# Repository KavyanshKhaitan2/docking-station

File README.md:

# (Overengineered) Laptop Docking Station!

  [View in OnShape](https://cad.onshape.com/documents/6c290d74c1d15daba79eec04/w/3858ccf09c2f651529fab3b7/e/cec4245d48316d051146b3ca?renderMode=0&uiState=6a2cddf3cc68f1e0ff63f0b2)

A very cool laptop docking station with 9 USB-A 2.0 ports!

<div id="contents">

1. [Why?](#why)
2. [What can it do?](#what-can-it-do)
3. [Fallout Zine](#fallout-zine)
4. [PCB](#pcb)
   - [Mainboard](#mainboard)
   - [Left Daughterboard](#left-daugtherboard)
5. [Schematic](#schematic)
   - [Mainboard](#mainboard-1)
   - [Left Daughterboard](#left-daugtherboard-1)
   - [Right Daugtherboard](#right-daugtherboard)
   - [Front Daugtherboard](#front-daughterboard)
6. [3D](#3d)
   - [Main case](#main-case)
   - [Macropad assembly](#macropad-assembly)
   - [Macropad case](#macropad-case)
   - [ePaper assembly](#epaper-assembly)
   - [ePaper case](#epaper-case)
7. [Bill of Materials](#bom)

</div>

## Why?
My laptop only has 2 USB-A ports, which is honestly not enough especially when both of them are used up for a keyboard and mouse.

I made this docking station to change that.

Another reason I made this is that I kinda like taking my laptop with me and keep it on my lap while using it on the sofa sometimes, so a docking station kinda makes that easier so you only have to plug it in and then everything works!

<div align="center"><a href="#contents">Jump to contents</a></div>

## What can it do?
It has 9 USB ports, which you can connect whatever you want to. The USB ports are controlled using an Fe1.1s controller.

It also has an ESP32 and 2 controllable PWM case fans (with two mosfet so you can turn them completely off), to keep your laptop cool and prevent it from overheating.

I also added external power from a barrel jack, because the laptop wont be able to power so many USB ports, especially when things are connected to them.

There is also a programmable e-ink display, you can display the time, your notifications, the current speed of the fans, or even show specifically which USB ports are currently in use!

I also added a mini detachable macropad with three switches and a rotary encoder.

You can program the macropad's buttons to do whatever you want! The rotary encoder also works as a switch, so technically there are four switches. You can make the rotary encoder change the volume, fan speeds, etc!

The macropad is connected to the ESP32!

Oh and btw the ESP32 also supports WiFi incase you want it to show weather or something even when the laptop is turned off.

The ESP32 also knows exactly which ports are connected to devices at a time, so you can also make it show how many ports are in use, and how many are free, etc!

<div align="center"><a href="#contents">Jump to contents</a></div>

## Fallout Zine

[ [Download PDF](https://github.com/KavyanshKhaitan2/docking-station/raw/main/zine/Zine%20Print.pdf) ]

<div align="center"><a href="#contents">Jump to contents</a></div>

## PCB
<div align="center"><a href="https://kicanvas.org/?repo=https%3A%2F%2Fgithub.com%2FKavyanshKhaitan2%2Fdocking-station%2Ftree%2Fmain%2Fpcb%2F">View in KiCanvas</a></div>

### Mainboard

### Left Daugtherboard

The rest of the PCBs are very similar to the left daughterboard one, so I wont add them. If you still want to take a look at them, feel free to open the KiCanvas link!

<div align="center"><a href="#contents">Jump to contents</a></div>

## Schematic
<div align="center"><a href="https://kicanvas.org/?repo=https%3A%2F%2Fgithub.com%2FKavyanshKhaitan2%2Fdocking-station%2Ftree%2Fmain%2Fpcb%2F">View in KiCanvas</a></div>

### Mainboard

### Left daugtherboard

### Right daugtherboard

### Front daughterboard

<div align="center"><a href="#contents">Jump to contents</a></div>

## 3D
- [ [Download assembly as a STEP file](https://github.com/KavyanshKhaitan2/docking-station/blob/main/Final%20assembly.step) ]
- [ [Open Assembly in OnShape](https://cad.onshape.com/documents/6c290d74c1d15daba79eec04/w/3858ccf09c2f651529fab3b7/e/cec4245d48316d051146b3ca) ]

### Main case

- [View in OnShape](https://cad.onshape.com/documents/6c290d74c1d15daba79eec04/w/3858ccf09c2f651529fab3b7/e/84ca16973cb290fcea814d7e)
  - Part 1 (bottom) ([View STL in GitHub](https://github.com/KavyanshKhaitan2/docking-station/blob/main/production/3dp/Main%20Case/Main%20Case%20Thingy%20-%20Part%201.stl))
    - Print in black
    - Please print this part with supports!
  - Part 2 (top) ([View STL in GitHub](https://github.com/KavyanshKhaitan2/docking-station/blob/main/production/3dp/Main%20Case/Main%20Case%20Thingy%20-%20Part%202.stl))
    - Print in black

<div align="center"><a href="#contents">Jump to contents</a></div>

### Macropad assembly

- [View in OnShape](https://cad.onshape.com/documents/6c290d74c1d15daba79eec04/w/3858ccf09c2f651529fab3b7/e/eab1af3c6609ed024df62d84)

### Macropad case

- [View in OnShape](https://cad.onshape.com/documents/6c290d74c1d15daba79eec04/w/3858ccf09c2f651529fab3b7/e/cd5c69b8e6d2878261d109a7)
  - Part 1 (bottom) ([View STL in GitHub](https://github.com/KavyanshKhaitan2/docking-station/blob/main/production/3dp/Switches%20Case/Switches%20Case%20-%20Part%201.stl))
    - Print in black
  - Part 2 (top) ([View STL in GitHub](https://github.com/KavyanshKhaitan2/docking-station/blob/main/production/3dp/Switches%20Case/Switches%20Case%20-%20Part%202.stl))
    - Print in black
  - Screw ([View STL in GitHub](https://github.com/KavyanshKhaitan2/docking-station/blob/main/production/3dp/Switches%20Case/Switches%20Case%20-%20Screw%20(print%20x4).stl))
    - Print in black
    - Print x4
  - Accent (for top) ([View STL in GitHub](https://github.com/KavyanshKhaitan2/docking-station/blob/main/production/3dp/Switches%20Case/Switches%20Case%20-%20Accent.stl))
    - Print in filament closest to #8B2B2B.
      - 

<div align="center"><a href="#contents">Jump to contents</a></div>

### ePaper assembly

- [View in OnShape](https://cad.onshape.com/documents/6c290d74c1d15daba79eec04/w/3858ccf09c2f651529fab3b7/e/d050ad97f0686956ed070595)

### ePaper case

- Main part
  - [View in OnShape](https://cad.onshape.com/documents/6c290d74c1d15daba79eec04/w/3858ccf09c2f651529fab3b7/e/4e8279b7c40fa71bd8f46031)
  - Lid part (Lid) ([View STL in GitHub](https://github.com/KavyanshKhaitan2/docking-station/blob/main/production/3dp/ePaper%20Case/ePaper%20case%20-%20case-lid.stl))
  - Main part (Main) ([View STL in GitHub](https://github.com/KavyanshKhaitan2/docking-station/blob/main/production/3dp/ePaper%20Case/ePaper%20case%20-%20case-main.stl))
- Display angle-r
  - [View in OnShape](https://cad.onshape.com/documents/6c290d74c1d15daba79eec04/w/3858ccf09c2f651529fab3b7/e/b7b2b35c02b07108b093d455)
  - [View STL on GitHub](https://github.com/KavyanshKhaitan2/docking-station/blob/main/production/3dp/ePaper%20Case/Display%20angle-r%20-%20Part%201.stl)
    - Print in black
   
<div align="center"><a href="#contents">Jump to contents</a></div>

# BOM
The total BOM cost is ~167 USD.

- [ [View BOM.csv on GitHub](https://github.com/KavyanshKhaitan2/docking-station/blob/main/BOM.csv) ]
- [ [View BOM on Google Sheets (recommended)](https://docs.google.com/spreadsheets/d/10IkC0bF_AbRYA1OKs2MpRCw-cC0xSpxhRANUAgOrwtY/edit?gid=1294926540#gid=1294926540) ]

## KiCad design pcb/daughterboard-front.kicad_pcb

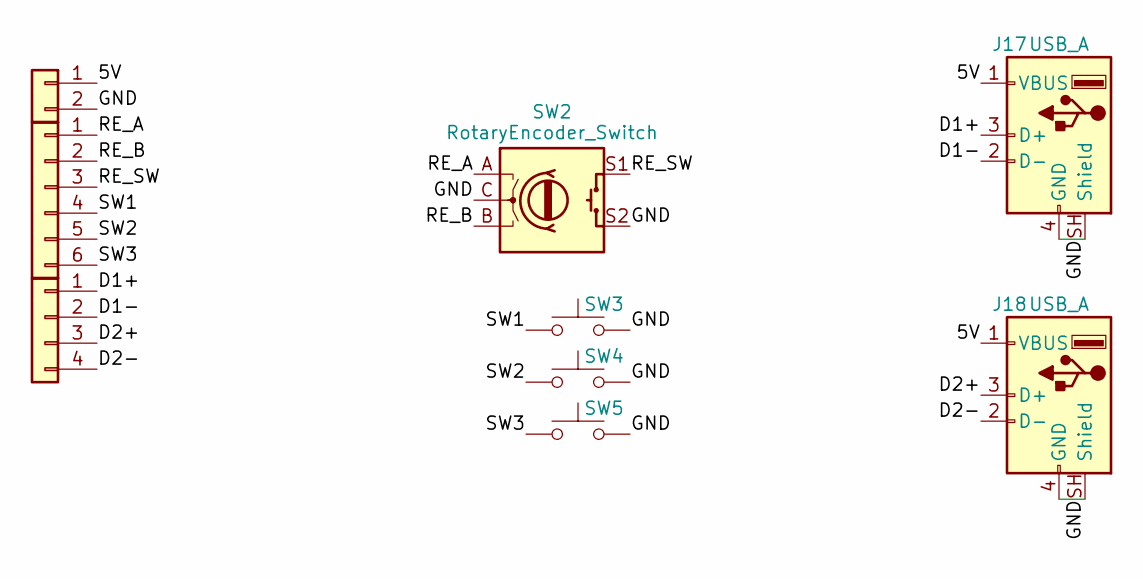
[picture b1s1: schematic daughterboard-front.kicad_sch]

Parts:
J16: Conn_01x06; PinHeader_1x06_P2.54mm_Vertical
J17, J18: USB_A; USB_A_Receptacle_GCT_USB1046
J26: Conn_01x04; Molex_200528-0040_1x04-1MP_P1.00mm_Horizontal
J31: Conn_01x02; SolderWire-4sqmm_1x02_P12mm_D3mm_OD6mm
SW2: RotaryEncoder_Switch; RotaryEncoder_Alps_EC11E-Switch_Vertical_H20mm
SW3, SW4, SW5: SW_Push; PinHeader_1x02_P2.54mm_Vertical

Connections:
/5V: J17.1 (VBUS), J18.1 (VBUS), J31.1
/D1+: J17.3 (D+), J26.1
/D1-: J17.2 (D-), J26.2
/D2+: J18.3 (D+), J26.3
/D2-: J18.2 (D-), J26.4
/GND: J17.4 (GND), J17.SH (Shield), J18.4 (GND), J18.SH (Shield), J31.2, SW2.C, SW2.S2, SW3.1, SW4.1, SW5.1
/RE_A: J16.1, SW2.A
/RE_B: J16.2, SW2.B
/RE_SW: J16.3, SW2.S1
/SW1: J16.4, SW3.2
/SW2: J16.5, SW4.2
/SW3: J16.6, SW5.2

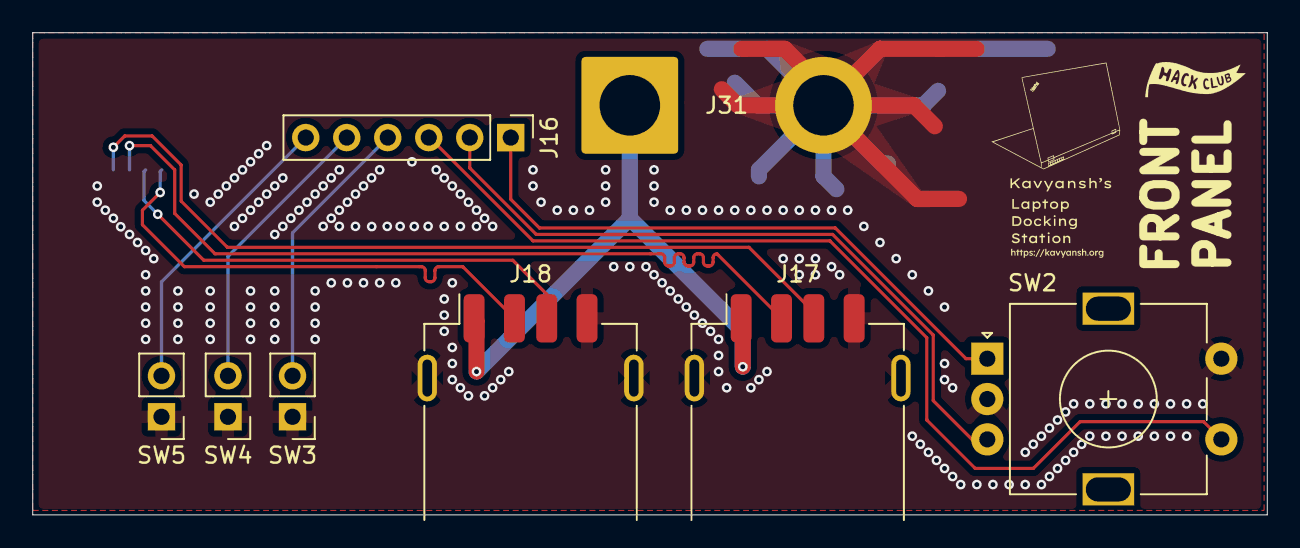
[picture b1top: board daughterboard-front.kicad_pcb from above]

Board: 2 copper layers, 76.5 x 29.9 mm, 9 parts (1 on the bottom side), 12 nets.

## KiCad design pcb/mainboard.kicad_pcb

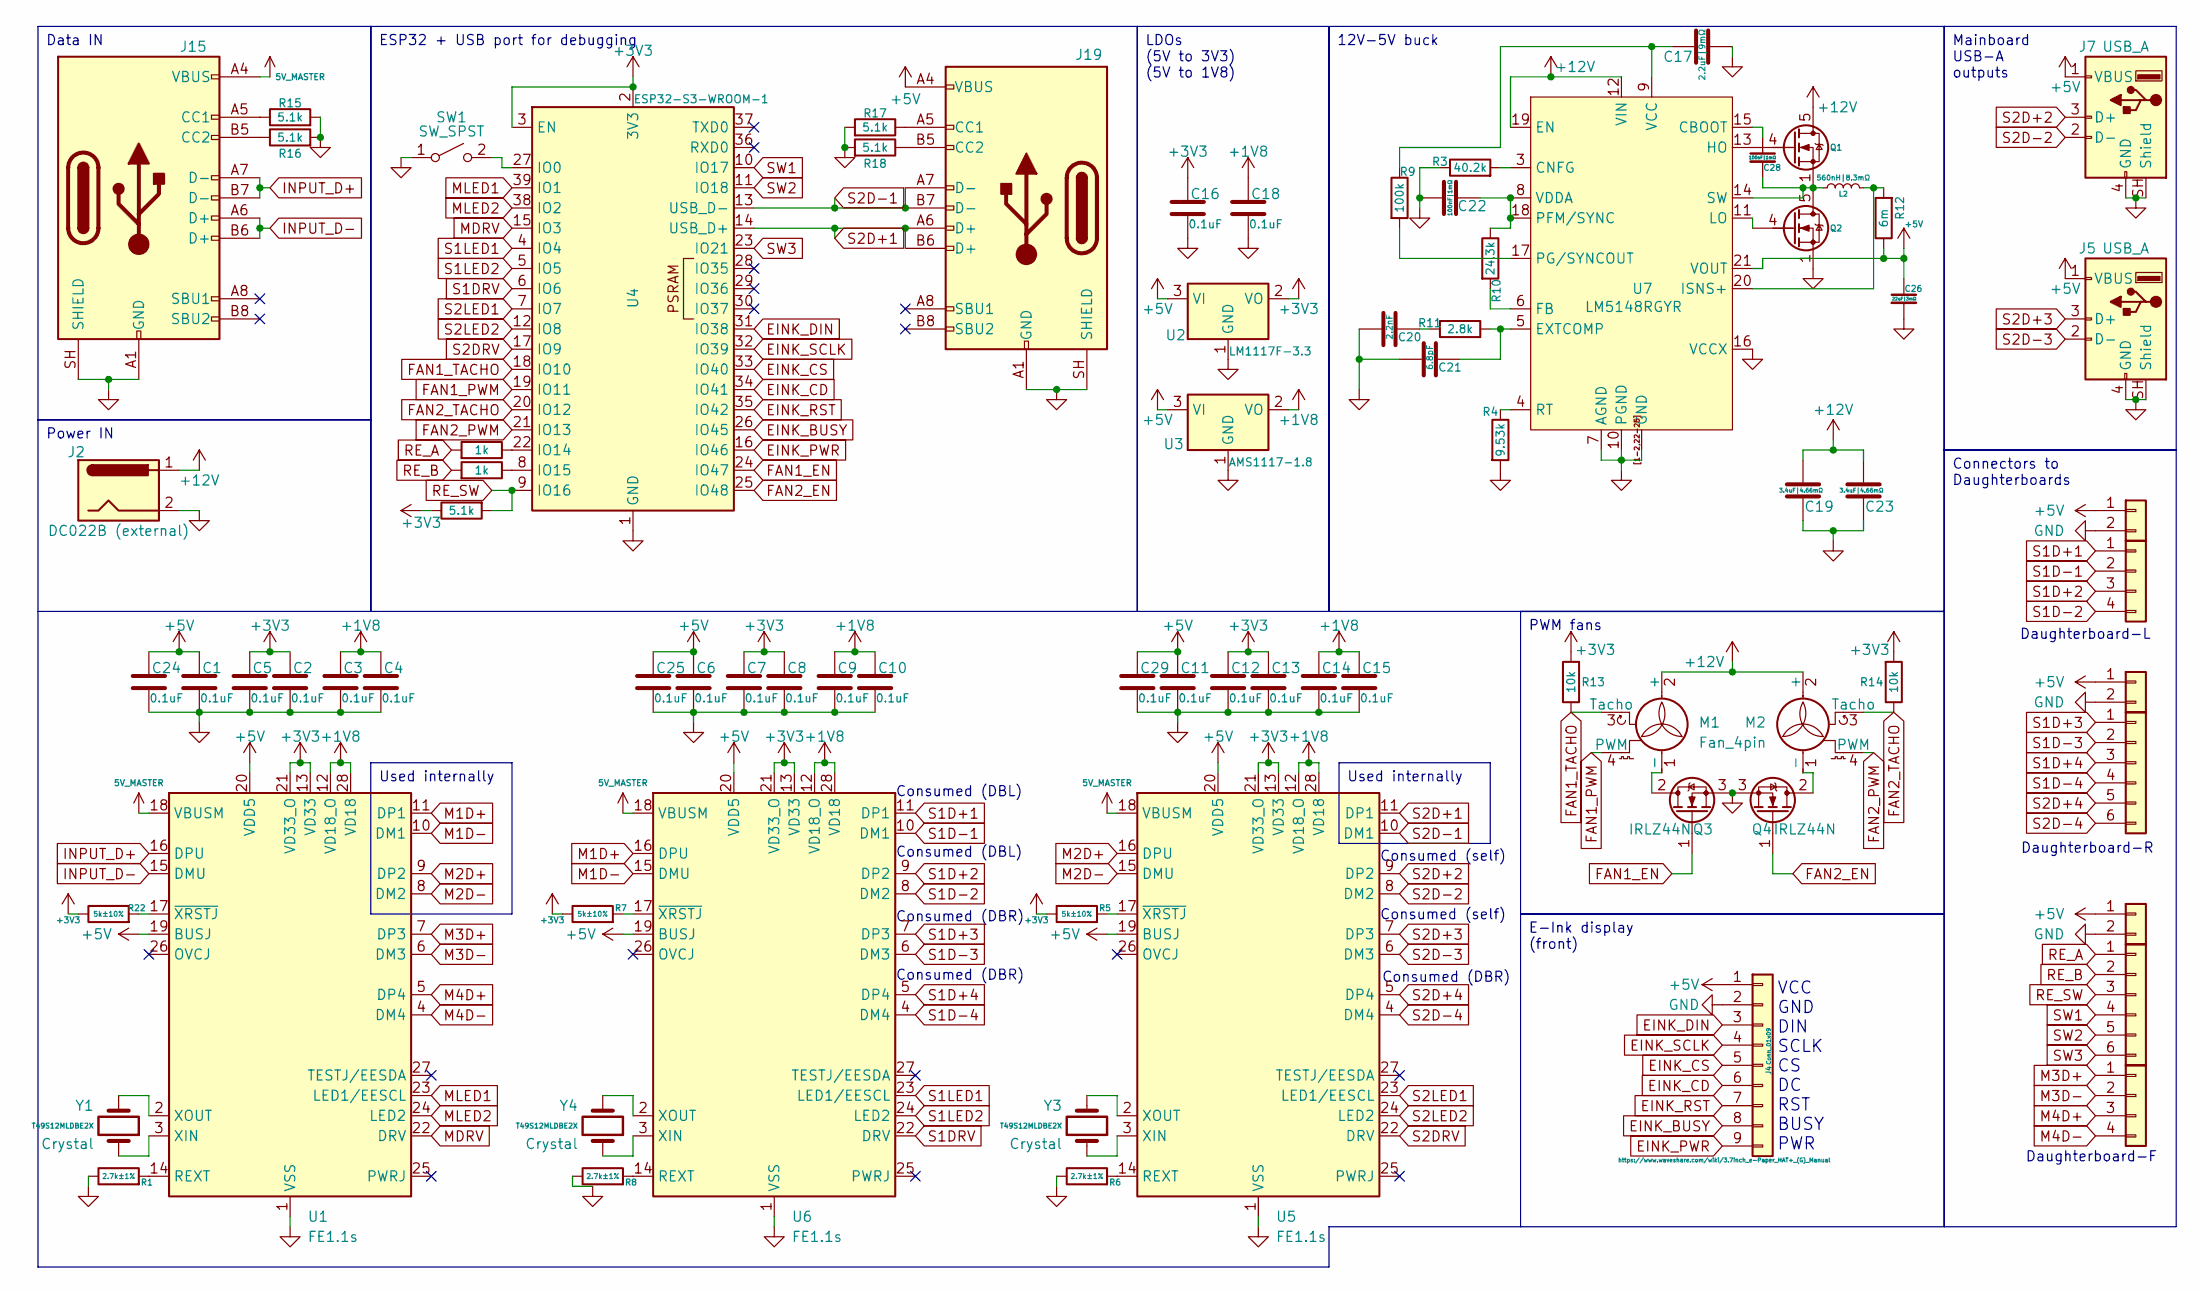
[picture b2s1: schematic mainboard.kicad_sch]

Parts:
C1, C2, C3, C4, C5, C6, C7, C8, C9, C10, C11, C12, C13, C14, C15, C16, C18, C24, C25, C29: 0.1uF; C_1206_3216Metric_Pad1.33x1.80mm_HandSolder
C17: 2.2uF|9mΩ; C_0603_1608Metric_Pad1.08x0.95mm_HandSolder
C19, C23: 3.4uF|4.66mΩ; C_1206_3216Metric_Pad1.33x1.80mm_HandSolder
C20: 2.2nF; C_0805_2012Metric_Pad1.18x1.45mm_HandSolder
C21: 6.8pF; C_0603_1608Metric_Pad1.08x0.95mm_HandSolder
C22, C28: 100nF|1mΩ; C_0402_1005Metric_Pad0.74x0.62mm_HandSolder
C26: 22uF|3mΩ; C_0805_2012Metric_Pad1.18x1.45mm_HandSolder
J2: DC022B (external); SolderWire-4sqmm_1x02_P12mm_D3mm_OD6mm
J4: Conn_01x09; JST_PH_B9B-PH-K_1x09_P2.00mm_Vertical
J5, J7: USB_A; USB_A_Receptacle_GCT_USB1046
J10: Conn_01x06; JUSHUO_AFA07-S06FCA-00_1x6-1MP_P1.0mm_Horizontal
J11: Conn_01x06; PinHeader_1x06_P2.54mm_Vertical
J15, J19: USB_C_Receptacle_USB2.0_16P; USB_C_Receptacle_HRO_TYPE-C-31-M-12
J20, J24, J27: Conn_01x02; SolderWire-4sqmm_1x02_P12mm_D3mm_OD6mm
J21, J25: Conn_01x04; Molex_200528-0040_1x04-1MP_P1.00mm_Horizontal
L2: 560nH|8.3mΩ; L_Coilcraft_XAL5020-XXX
M1, M2: Fan_4pin; FanPinHeader_1x04_P2.54mm_Vertical
Q1, Q2: CSD17579Q5A; TDSON-8-1
Q3, Q4: IRLZ44N; TO-220-3_Vertical
R1, R6, R8: 2.7k±1%; R_1206_3216Metric_Pad1.30x1.75mm_HandSolder
R3: 40.2k; R_1206_3216Metric_Pad1.30x1.75mm_HandSolder
R4: 9.53k; R_1206_3216Metric_Pad1.30x1.75mm_HandSolder
R5, R7, R22: 5k±10%; R_1206_3216Metric_Pad1.30x1.75mm_HandSolder
R9: 100k; R_1206_3216Metric_Pad1.30x1.75mm_HandSolder
R10: 24.3k; R_1206_3216Metric_Pad1.30x1.75mm_HandSolder
R11: 2.8k; R_1206_3216Metric_Pad1.30x1.75mm_HandSolder
R12: 6m; R_1206_3216Metric_Pad1.30x1.75mm_HandSolder
R13, R14: 10k; R_1206_3216Metric_Pad1.30x1.75mm_HandSolder
R15, R16, R17, R18, R21: 5.1k; R_1206_3216Metric_Pad1.30x1.75mm_HandSolder
R19, R20: 1k; R_1206_3216Metric_Pad1.30x1.75mm_HandSolder
SW1: SW_SPST; SW_SPST_Omron_B3F-50xx
U1, U5, U6: FE1.1s; SSOP-28_3.9x9.9mm_P0.635mm
U2: LM1117F-3.3; SOT-89-3_Handsoldering
U3: AMS1117-1.8; SOT-89-3_Handsoldering
U4: ESP32-S3-WROOM-1
U7: LM5148RGYR; Texas_RGY_R-PVQFN-N24_EP2.05x3.1mm_ThermalVias
Y1, Y3, Y4: T49S12MLDBE2X; Crystal_HC49-4H_Vertical

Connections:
5V_MASTER: J15.A4 (VBUS), J15.A9 (VBUS), J15.B4 (VBUS), J15.B9 (VBUS), U1.18 (VBUSM), U5.18 (VBUSM), U6.18 (VBUSM)
+1V8: C3.1, C4.1, C9.1, C10.1, C14.1, C15.1, C18.1, U1.12 (VD18_O), U1.28 (VD18), U3.2 (VO), U5.12 (VD18_O), U5.28 (VD18), U6.12 (VD18_O), U6.28 (VD18)
+3V3: C2.1, C5.1, C7.1, C8.1, C12.1, C13.1, C16.1, R5.1, R7.1, R13.2, R14.2, R21.1, R22.1, U1.13 (VD33), U1.21 (VD33_O), U2.2 (VO), U4.2 (3V3), U4.3 (EN), U5.13 (VD33), U5.21 (VD33_O), U6.13 (VD33), U6.21 (VD33_O)
+5V: C1.1, C6.1, C11.1, C24.1, C25.1, C26.1, C29.1, J4.1, J5.1 (VBUS), J7.1 (VBUS), J19.A4 (VBUS), J19.A9 (VBUS), J19.B4 (VBUS), J19.B9 (VBUS), J20.1, J24.1, J27.1, R12.1, U1.19 (BUSJ), U1.20 (VDD5), U2.3 (VI), U3.3 (VI), U5.19 (BUSJ), U5.20 (VDD5), U6.19 (BUSJ), U6.20 (VDD5), U7.21 (VOUT)
+12V: C19.2, C23.2, J2.1, M1.2 (+), M2.2 (+), Q1.5 (D), U7.12 (VIN), U7.19 (EN)
EINK_BUSY: J4.8, U4.26 (IO45)
EINK_CD: J4.6, U4.34 (IO41)
EINK_CS: J4.5, U4.33 (IO40)
EINK_DIN: J4.3, U4.31 (IO38)
EINK_PWR: J4.9, U4.16 (IO46)
EINK_RST: J4.7, U4.35 (IO42)
EINK_SCLK: J4.4, U4.32 (IO39)
FAN1_EN: Q3.1 (G), U4.24 (IO47)
FAN1_PWM: M1.4 (PWM), U4.19 (IO11)
FAN1_TACHO: M1.3 (Tacho), R13.1, U4.18 (IO10)
FAN2_EN: Q4.1 (G), U4.25 (IO48)
FAN2_PWM: M2.4 (PWM), U4.21 (IO13)
FAN2_TACHO: M2.3 (Tacho), R14.1, U4.20 (IO12)
GND: C1.2, C2.2, C3.2, C4.2, C5.2, C6.2, C7.2, C8.2, C9.2, C10.2, C11.2, C12.2, C13.2, C14.2, C15.2, C16.2, C17.1, C18.2, C19.1, C20.2, C21.2, C22.2, C23.1, C24.2, C25.2, C26.2, C29.2, J2.2, J4.2, J5.4 (GND), J5.SH (Shield), J7.4 (GND), J7.SH (Shield), J15.A1 (GND), J15.A12 (GND), J15.B1 (GND), J15.B12 (GND), J15.SH (SHIELD), J19.A1 (GND), J19.A12 (GND), J19.B1 (GND), J19.B12 (GND), J19.SH (SHIELD), J20.2, J24.2, J27.2, Q2.1 (S), Q2.2 (S), Q2.3 (S), Q3.3 (S), Q4.3 (S), R1.1, R3.1, R4.2, R6.1, R8.1, R15.2, R16.2, R17.2, R18.2, SW1.1 (A), U1.1 (VSS), U2.1 (GND), U3.1 (GND), U4.1 (GND), U4.40 (GND), U4.41 (GND), U5.1 (VSS), U6.1 (VSS), U7.1 (GND), U7.2 (GND), U7.7 (AGND), U7.10 (PGND), U7.16 (VCCX), U7.22 (GND), U7.23 (GND), U7.24 (GND), U7.25 (GND), U7.[1-2,22-25] (GND)
INPUT_D+: J15.A7 (D-), J15.B7 (D-), U1.16 (DPU)
INPUT_D-: J15.A6 (D+), J15.B6 (D+), U1.15 (DMU)
M1D+: U1.11 (DP1), U6.16 (DPU)
M1D-: U1.10 (DM1), U6.15 (DMU)
M2D+: U1.9 (DP2), U5.16 (DPU)
M2D-: U1.8 (DM2), U5.15 (DMU)
M3D+: J25.1, U1.7 (DP3)
M3D-: J25.2, U1.6 (DM3)
M4D+: J25.3, U1.5 (DP4)
M4D-: J25.4, U1.4 (DM4)
MDRV: U1.22 (DRV), U4.15 (IO3)
MLED1: U1.23 (LED1/EESCL), U4.39 (IO1)
MLED2: U1.24 (LED2), U4.38 (IO2)
unnamed: C20.1, R11.1
unnamed: J15.A5 (CC1), R15.1
unnamed: J15.B5 (CC2), R16.1
unnamed: J19.A5 (CC1), R17.1
unnamed: J19.B5 (CC2), R18.1
unnamed: M1.1 (-), Q3.2 (D)
unnamed: M2.1 (-), Q4.2 (D)
unnamed: Q1.4 (G), U7.13 (HO)
unnamed: C28.2, L2.1, Q1.1 (S), Q1.2 (S), Q1.3 (S), Q2.5 (D), U7.14 (SW)
unnamed: Q2.4 (G), U7.11 (LO)
unnamed: SW1.2 (B), U4.27 (IO0)
unnamed: R1.2, U1.14 (REXT)
unnamed: U1.3 (XIN), Y1.1
unnamed: U1.2 (XOUT), Y1.2
unnamed: R22.2, U1.17 (~XRSTJ)
unnamed: R19.1, U4.22 (IO14)
unnamed: R20.1, U4.8 (IO15)
unnamed: R6.2, U5.14 (REXT)
unnamed: U5.3 (XIN), Y3.1
unnamed: U5.2 (XOUT), Y3.2
unnamed: R5.2, U5.17 (~XRSTJ)
unnamed: R8.2, U6.14 (REXT)
unnamed: U6.3 (XIN), Y4.1
unnamed: U6.2 (XOUT), Y4.2
unnamed: R7.2, U6.17 (~XRSTJ)
unnamed: C28.1, U7.15 (CBOOT)
unnamed: R3.2, U7.3 (CNFG)
unnamed: C21.1, R11.2, U7.5 (EXTCOMP)
unnamed: R10.2, U7.6 (FB)
unnamed: L2.2, R12.2, U7.20 (ISNS+)
unnamed: C22.1, R10.1, U7.8 (VDDA), U7.18 (PFM/SYNC)
unnamed: R9.2, U7.17 (PG/SYNCOUT)
unnamed: R4.1, U7.4 (RT)
unnamed: C17.2, R9.1, U7.9 (VCC)
RE_A: J11.1, R19.2
RE_B: J11.2, R20.2
RE_SW: J11.3, R21.2, U4.9 (IO16)
S1D+1: J21.1, U6.11 (DP1)
S1D+2: J21.3, U6.9 (DP2)
S1D+3: J10.1, U6.7 (DP3)
S1D+4: J10.3, U6.5 (DP4)
S1D-1: J21.2, U6.10 (DM1)
S1D-2: J21.4, U6.8 (DM2)
S1D-3: J10.2, U6.6 (DM3)
S1D-4: J10.4, U6.4 (DM4)
S1DRV: U4.6 (IO6), U6.22 (DRV)
S1LED1: U4.4 (IO4), U6.23 (LED1/EESCL)
S1LED2: U4.5 (IO5), U6.24 (LED2)
S2D+1: J19.A6 (D+), J19.B6 (D+), U4.14 (USB_D+), U5.11 (DP1)
S2D+2: J7.3 (D+), U5.9 (DP2)
S2D+3: J5.3 (D+), U5.7 (DP3)
S2D+4: J10.5, U5.5 (DP4)
S2D-1: J19.A7 (D-), J19.B7 (D-), U4.13 (USB_D-), U5.10 (DM1)
S2D-2: J7.2 (D-), U5.8 (DM2)
S2D-3: J5.2 (D-), U5.6 (DM3)
S2D-4: J10.6, U5.4 (DM4)
S2DRV: U4.17 (IO9), U5.22 (DRV)
S2LED1: U4.7 (IO7), U5.23 (LED1/EESCL)
S2LED2: U4.12 (IO8), U5.24 (LED2)
SW1: J11.4, U4.10 (IO17)
SW2: J11.5, U4.11 (IO18)
SW3: J11.6, U4.23 (IO21)

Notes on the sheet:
Consumed (DBR)
Consumed (self)
Daughterboard-F
Consumed (DBL)
Daughterboard-R
VCC GND DIN SCLK CS DC RST BUSY PWR
Daughterboard-L
Used internally
Mainboard USB-A outputs
E-Ink display (front)
Data IN
Connectors to Daughterboards
ESP32 + USB port for debugging
Power IN
PWM fans
LDOs (5V to 3V3) (5V to 1V8)
12V-5V buck

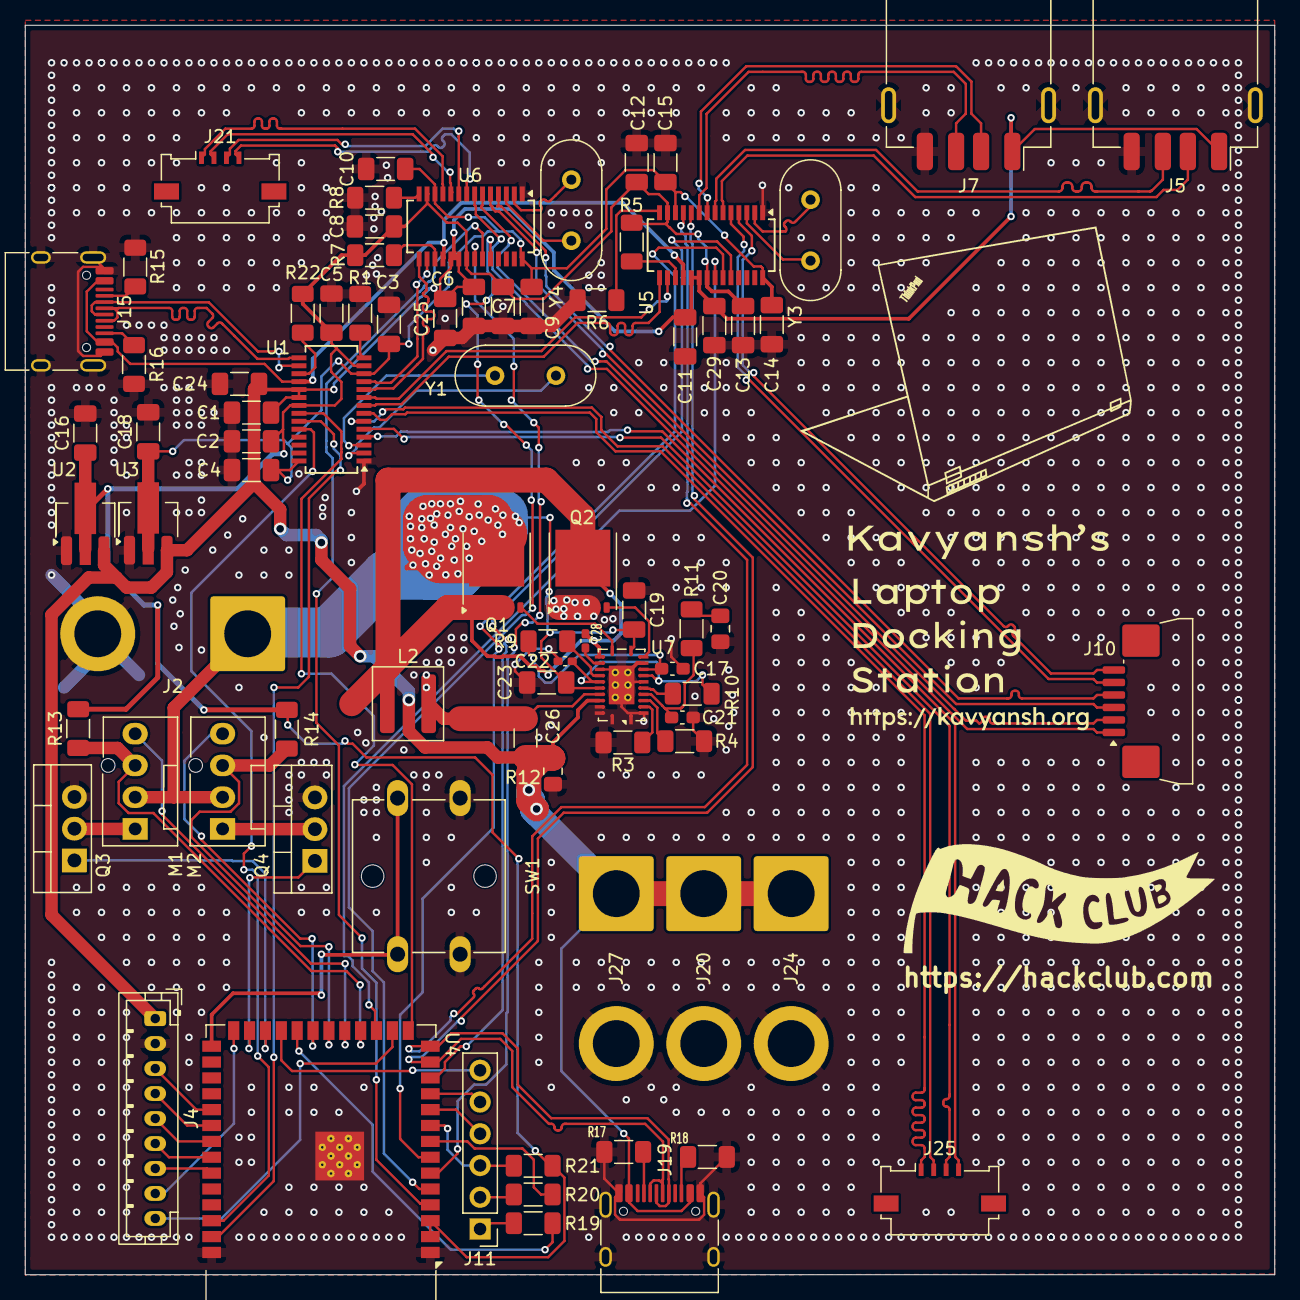
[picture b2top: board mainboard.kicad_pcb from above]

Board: 2 copper layers, 100.0 x 100.0 mm, 80 parts (0 on the bottom side), 94 nets.

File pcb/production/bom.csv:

Designator,Footprint,Quantity,Value,LCSC Part #
"C1, C10, C11, C12, C13, C14, C15, C16, C18, C2, C24, C25, C29, C3, C4, C5, C6, C7, C8, C9",1206,20,0.1uF,
C17,0603,1,2.2uF|9mΩ,
"C19, C23",1206,2,3.4uF|4.66mΩ,
C20,0805,1,2.2nF,
C21,0603,1,6.8pF,
"C22, C28",0402,2,100nF|1mΩ,
C26,0805,1,22uF|3mΩ,
J10,JUSHUO_AFA07-S06FCA-00_1x6-1MP_P1.0mm_Horizontal,1,Conn_01x06,
J11,PinHeader_1x06_P2.54mm_Vertical,1,Conn_01x06,
"J15, J19",USB_C_Receptacle_HRO_TYPE-C-31-M-12,2,USB_C_Receptacle_USB2.0_16P,
J2,SolderWire-4sqmm_1x02_P12mm_D3mm_OD6mm,1,DC022B (external),
"J20, J24, J27",SolderWire-4sqmm_1x02_P12mm_D3mm_OD6mm,3,Conn_01x02,
"J21, J25",Molex_200528-0040_1x04-1MP_P1.00mm_Horizontal,2,Conn_01x04,
J4,JST_PH_B9B-PH-K_1x09_P2.00mm_Vertical,1,Conn_01x09,
"J5, J7",USB_A_Receptacle_GCT_USB1046,2,USB_A,
L2,L_Coilcraft_XAL5020-XXX,1,560nH|8.3mΩ,
"M1, M2",FanPinHeader_1x04_P2.54mm_Vertical,2,Fan_4pin,
"Q1, Q2",TDSON-8-1,2,CSD17579Q5A,
"Q3, Q4",TO-220-3_Vertical,2,IRLZ44N,
"R1, R6, R8",1206,3,2.7k±1%,
R10,1206,1,24.3k,
R11,1206,1,2.8k,
R12,1206,1,6m,
"R13, R14",1206,2,10k,
"R15, R16, R17, R18, R21",1206,5,5.1k,
"R19, R20",1206,2,1k,
"R22, R5, R7",1206,3,5k±10%,
R3,1206,1,40.2k,
R4,1206,1,9.53k,
R9,1206,1,100k,
SW1,SW_SPST_Omron_B3F-50xx,1,SW_SPST,
"U1, U5, U6",SSOP-28_3.9x9.9mm_P0.635mm,3,FE1.1s,
U2,SOT-89-3_Handsoldering,1,LM1117F-3.3,
U3,SOT-89-3_Handsoldering,1,AMS1117-1.8,
U4,ESP32-S3-WROOM-1,1,ESP32-S3-WROOM-1,
U7,Texas_RGY_R-PVQFN-N24_EP2.05x3.1mm_ThermalVias,1,LM5148RGYR,
"Y1, Y3, Y4",Crystal_HC49-4H_Vertical,3,T49S12MLDBE2X,

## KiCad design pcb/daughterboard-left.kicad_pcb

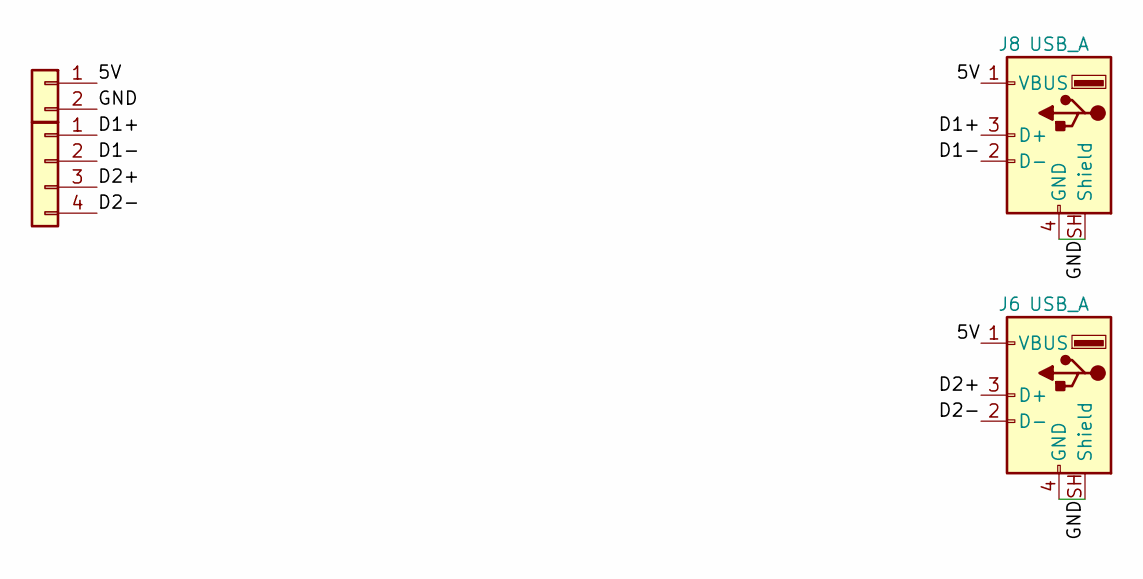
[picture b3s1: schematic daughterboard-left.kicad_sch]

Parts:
J6, J8: USB_A; USB_A_Receptacle_GCT_USB1046
J22: Conn_01x02; SolderWire-4sqmm_1x02_P12mm_D3mm_OD6mm
J23: Conn_01x04; Molex_200528-0040_1x04-1MP_P1.00mm_Horizontal

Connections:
/5V: J6.1 (VBUS), J8.1 (VBUS), J22.1
/D1+: J8.3 (D+), J23.1
/D1-: J8.2 (D-), J23.2
/D2+: J6.3 (D+), J23.3
/D2-: J6.2 (D-), J23.4
/GND: J6.4 (GND), J6.SH (Shield), J8.4 (GND), J8.SH (Shield), J22.2

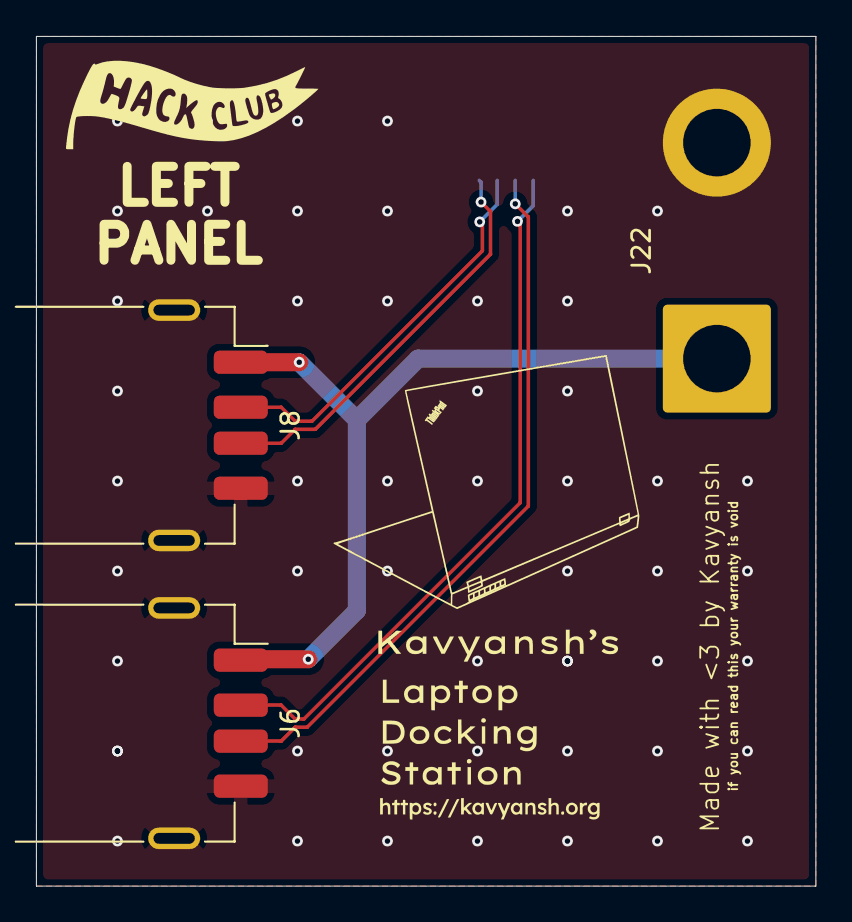
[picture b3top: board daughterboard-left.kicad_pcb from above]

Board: 2 copper layers, 43.3 x 47.2 mm, 4 parts (1 on the bottom side), 6 nets.

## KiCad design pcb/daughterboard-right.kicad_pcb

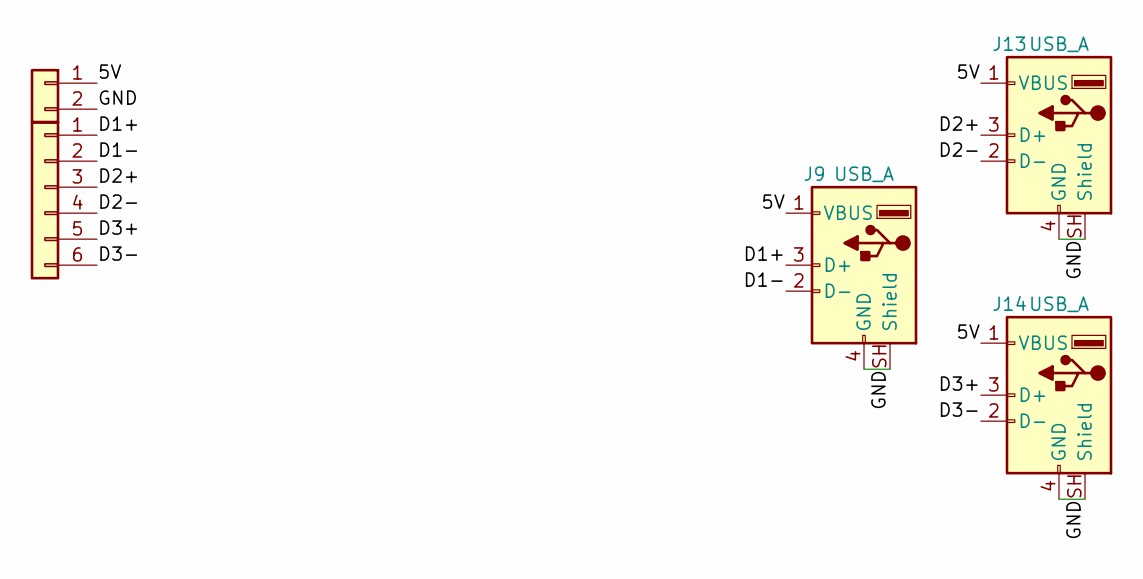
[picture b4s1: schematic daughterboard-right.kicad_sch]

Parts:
J9, J13, J14: USB_A; USB_A_Receptacle_GCT_USB1046
J12: Conn_01x06; JUSHUO_AFA07-S06FCA-00_1x6-1MP_P1.0mm_Horizontal
J30: Conn_01x02; SolderWire-4sqmm_1x02_P12mm_D3mm_OD6mm

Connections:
/5V: J9.1 (VBUS), J13.1 (VBUS), J14.1 (VBUS), J30.1
/D1+: J9.3 (D+), J12.1
/D1-: J9.2 (D-), J12.2
/D2+: J12.3, J13.3 (D+)
/D2-: J12.4, J13.2 (D-)
/D3+: J12.5, J14.3 (D+)
/D3-: J12.6, J14.2 (D-)
/GND: J9.4 (GND), J9.SH (Shield), J13.4 (GND), J13.SH (Shield), J14.4 (GND), J14.SH (Shield), J30.2

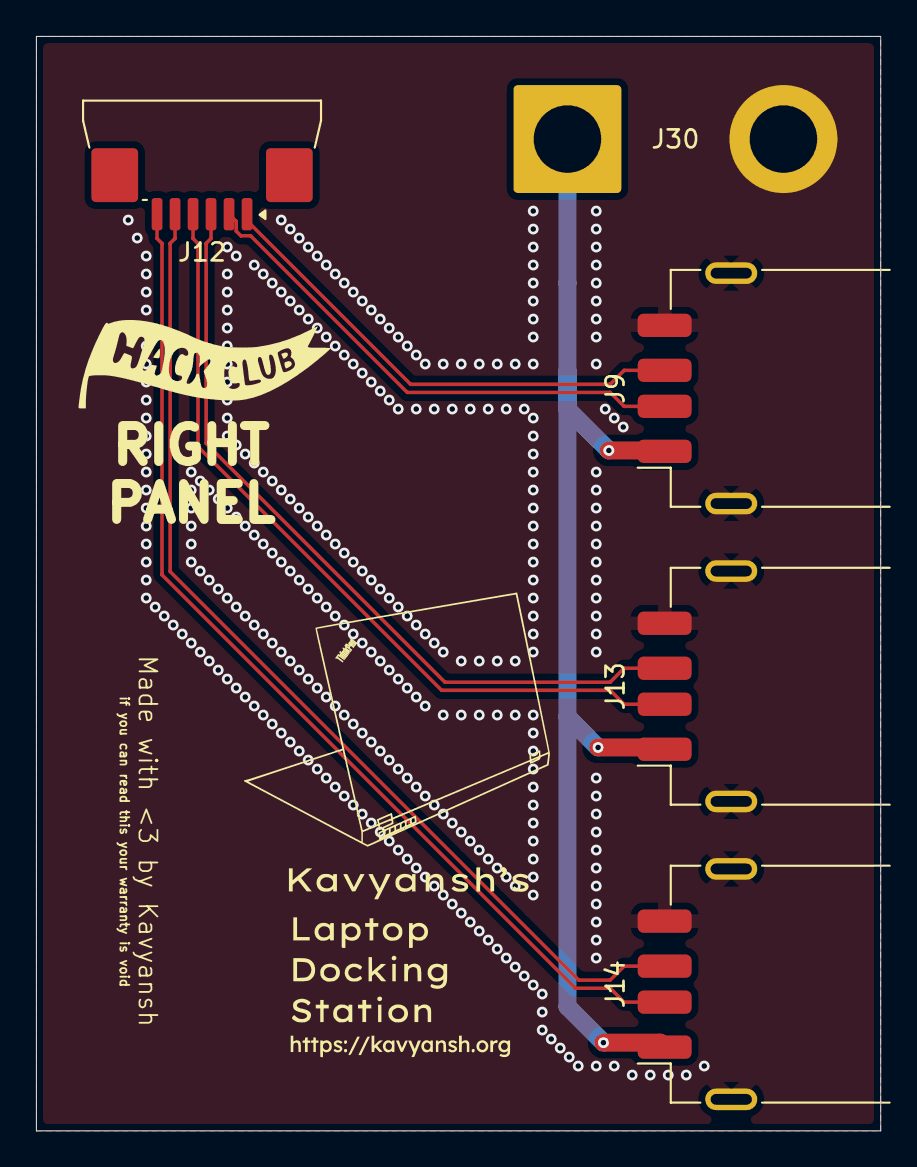
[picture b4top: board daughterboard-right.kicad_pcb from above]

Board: 2 copper layers, 46.9 x 60.8 mm, 5 parts (0 on the bottom side), 8 nets.

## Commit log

2026-06-12 Add PCB
2026-06-12 Add zine
2026-06-12 Remove .lck file from ./pcb
2026-06-12 Add production/3dp
2026-06-12 Add production README
2026-06-13 Create README.md for docking station project
    Added detailed information about the docking station, including features, functionality, and links to additional resources.
2026-06-13 Add BOM.csv
2026-06-13 Update README with PCB, Schematic, 3D, and BOM sections
    Added sections for PCB, Schematic, 3D models, and BOM with links.
2026-06-13 Add Bill of Materials section to README
2026-06-13 Change Zine
2026-06-13 Update project title to include 'Overengineered'
2026-06-13 Update project title to 'Laptop Docking Station'
